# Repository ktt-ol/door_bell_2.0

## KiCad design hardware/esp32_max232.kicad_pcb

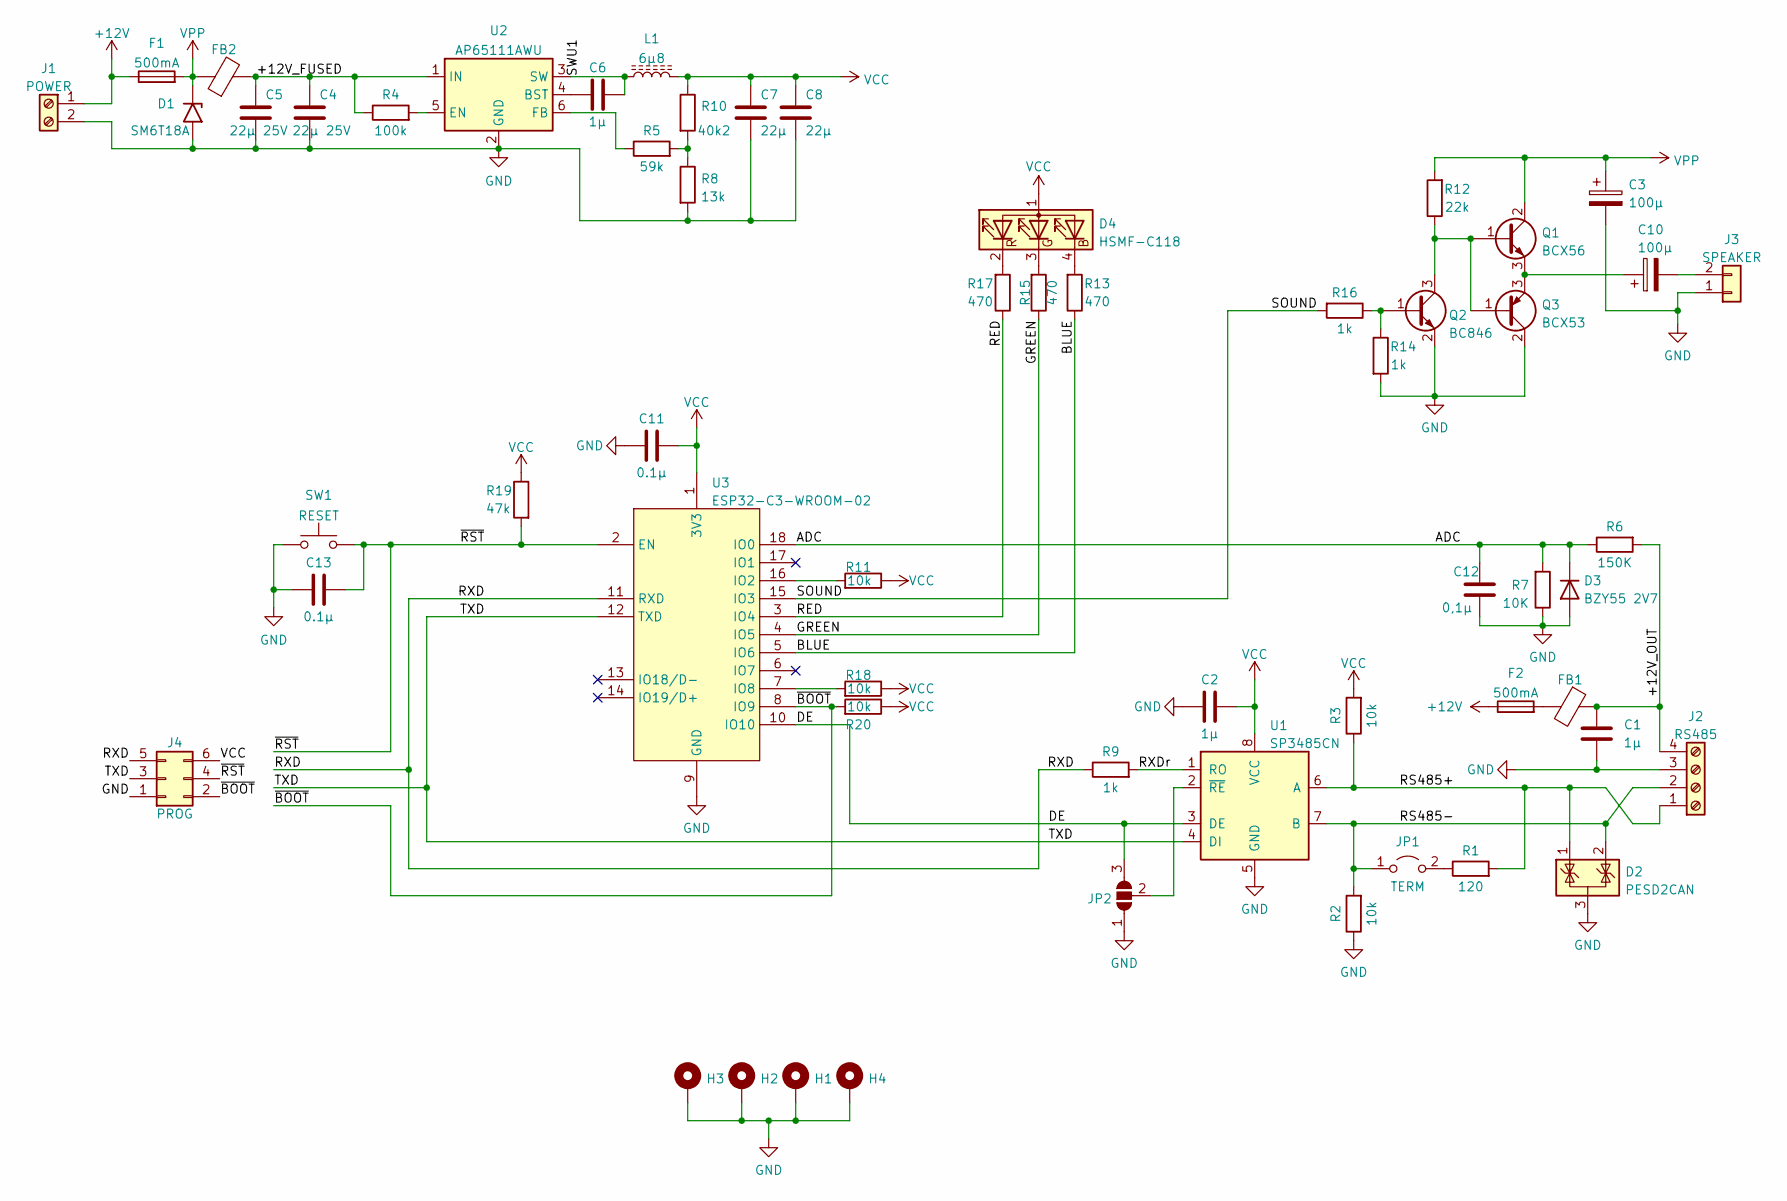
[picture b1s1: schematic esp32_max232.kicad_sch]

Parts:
C1, C2, C6: 1µ; C_0805_2012Metric
C3, C10: 100µ; CP_EIA-7343-31_Kemet-D
C4, C5: 22µ 25V; C_0805_2012Metric
C7, C8: 22µ; C_0805_2012Metric
C11, C13: 0.1µ; C_0805_2012Metric
C12: 0,1µ; C_0805_2012Metric
D1: SM6T18A; D_SMB
D2: PESD2CAN; SOT-23
D3: BZY55 2V7; D_0805_2012Metric
D4: HSMF-C118; LED_RGB_1210
F1, F2: 500mA; Fuse_0805_2012Metric_Pad1.15x1.40mm_HandSolder
FB1, FB2: FerriteBead; L_0805_2012Metric
H1, H2, H3, H4: MountingHole_Pad; MountingHole_3.2mm_M3_ISO7380_Pad_TopBottom
J1: POWER; TerminalBlock_RND_205-00001_1x02_P5.00mm_Horizontal
J2: RS485; TerminalBlock_RND_205-00003_1x04_P5.00mm_Horizontal
J3: SPEAKER; JST_EH_B2B-EH-A_1x02_P2.50mm_Vertical
J4: PROG; PinHeader_2x03_P2.54mm_Vertical
JP1: TERM; PinHeader_1x02_P2.54mm_Vertical
JP2: SolderJumper_3_Open; SolderJumper-3_P2.0mm_Open_TrianglePad1.0x1.5mm
L1: 6µ8; L_Taiyo-Yuden_NR-50xx
Q1: BCX56; SOT-89-3
Q2: BC846; SOT-23
Q3: BCX53; SOT-89-3
R1: 120; R_0805_2012Metric
R2, R3, R11, R18, R20: 10k; R_0805_2012Metric
R4: 100k; R_0805_2012Metric
R5: 59k; R_0805_2012Metric
R6: 150K; R_0805_2012Metric
R7: 10K; R_0805_2012Metric
R8: 13k; R_0805_2012Metric
R9, R14, R16: 1k; R_0805_2012Metric
R10: 40k2; R_0805_2012Metric
R12: 22k; R_0805_2012Metric
R13, R15, R17: 470; R_0805_2012Metric
R19: 47k; R_0805_2012Metric
SW1: RESET; SW_SPST_PTS810
U1: SP3485CN; SOIC-8_3.9x4.9mm_P1.27mm
U2: AP65111AWU; TSOT-23-6
U3: ESP32-C3-WROOM-02; ESP-WROOM-02

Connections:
+12V: F1.1, F2.1, J1.1
/+12V_FUSED: C4.1, C5.1, FB2.2, R4.1, U2.1 (IN)
/+12V_OUT: C1.2, FB1.1, J2.4, R6.2
/ADC: C12.1, D3.1 (K), R6.1, R7.2, U3.18 (IO0)
/BLUE: R13.1, U3.5 (IO6)
/DE: JP2.3 (B), U1.3 (DE), U3.10 (IO10)
/GREEN: R15.1, U3.4 (IO5)
/RED: R17.1, U3.3 (IO4)
/RS485+: D2.1 (K), J2.1, R1.2, R3.1, U1.6 (A)
/RS485-: D2.2 (K), J2.2, JP1.1 (A), R2.2, U1.7 (B)
/RXD: J4.5, R9.1, U3.11 (RXD)
/RXDr: R9.2, U1.1 (RO)
/SOUND: R16.2, U3.15 (IO3)
/SWU1: C6.2, L1.1, U2.3 (SW)
/TXD: J4.3, U1.4 (DI), U3.12 (TXD)
/~BOOT: J4.2, R20.2, U3.8 (IO9)
/~RST: C13.1, J4.4, R19.2, SW1.1, U3.2 (EN)
GND: C1.1, C2.2, C3.2, C4.2, C5.2, C7.2, C8.2, C11.2, C12.2, C13.2, D1.2 (A2), D2.3 (A), D3.2 (A), H1.1, H2.1, H3.1, H4.1, J1.2, J2.3, J3.1, J4.1, JP2.1 (A), Q2.2 (E), Q3.2 (C), R2.1, R7.1, R8.2, R14.2, SW1.2, U1.5 (GND), U2.2 (GND), U3.9 (GND), U3.19 (GND)
unnamed: C6.1, U2.4 (BST)
unnamed: C10.1, Q1.3 (E), Q3.3 (E)
unnamed: C10.2, J3.2
unnamed: D4.2 (RK), R17.2
unnamed: D4.3 (GK), R15.2
unnamed: D4.4 (BK), R13.2
unnamed: F2.2, FB1.2
unnamed: JP1.2 (B), R1.1
unnamed: JP2.2 (C), U1.2 (~RE)
unnamed: Q1.1 (B), Q2.3 (C), Q3.1 (B), R12.1
unnamed: Q2.1 (B), R14.1, R16.1
unnamed: R4.2, U2.5 (EN)
unnamed: R5.1, U2.6 (FB)
unnamed: R5.2, R8.1, R10.2
unnamed: R11.2, U3.16 (IO2)
unnamed: R18.2, U3.7 (IO8)
VCC: C2.1, C7.1, C8.1, C11.1, D4.1 (A), J4.6, L1.2, R3.2, R10.1, R11.1, R18.1, R19.1, R20.1, U1.8 (VCC), U3.1 (3V3)
VPP: C3.1, D1.1 (A1), F1.2, FB2.1, Q1.2 (C), R12.2

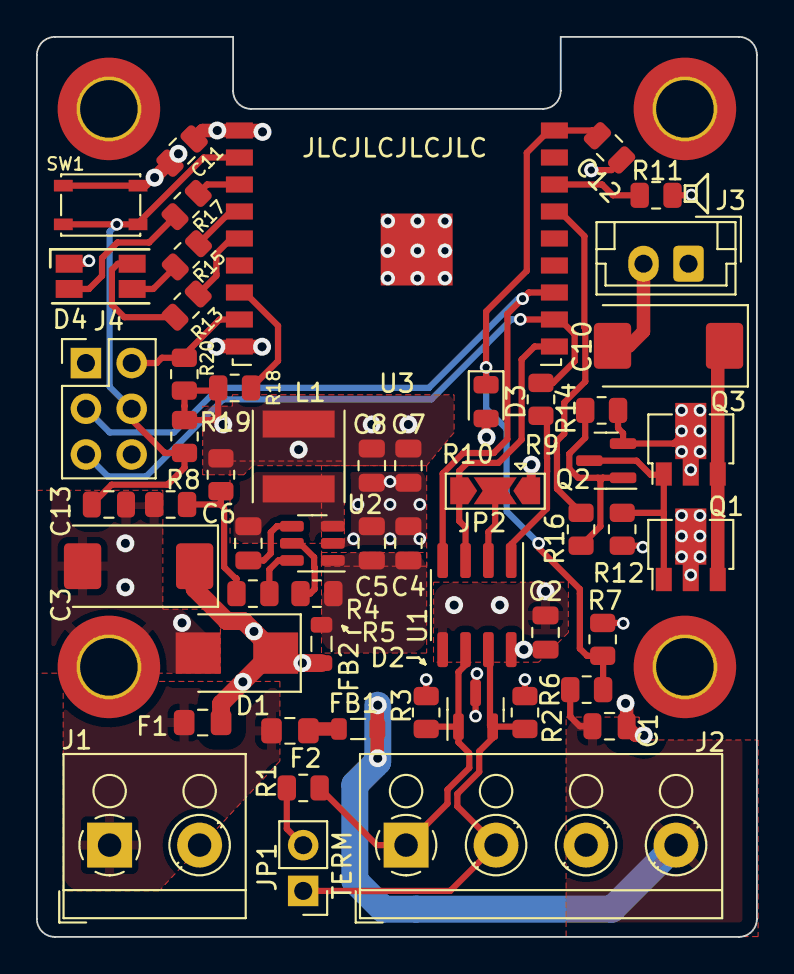
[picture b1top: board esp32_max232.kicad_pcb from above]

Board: 4 copper layers, 40.0 x 50.0 mm, 58 parts (0 on the bottom side), 36 nets.

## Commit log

2023-03-01 Initial commit of Top module
2023-10-24 Rename top level directory
2023-10-24 Add compile script
2023-10-24 Formatting cleanup
2023-10-24 Definitions cleanup
2023-10-24 Eliminate idle noise
2023-10-24 Give feedback when playing sound
2023-10-24 Refactor LED handling
2023-10-24 Add silence period
2023-10-24 Increase timer size up to 64 bit
2023-11-03 Adopt status_next logic
2023-11-04 Add NTP support
2023-11-04 Add sophisticated MQTT reconnect handling
2023-11-04 Observe MQTT status failures
2023-11-04 Support bus monitoring and panic
2023-11-05 Improve bus arbiter precision
2023-11-05 Add dummy cpp files
2023-11-05 Add bus idle detection
2023-11-12 Generate different MQTT IDs at connect
2023-11-12 Do not send "disconnected" repeatedly
2024-01-23 Add hardware project
